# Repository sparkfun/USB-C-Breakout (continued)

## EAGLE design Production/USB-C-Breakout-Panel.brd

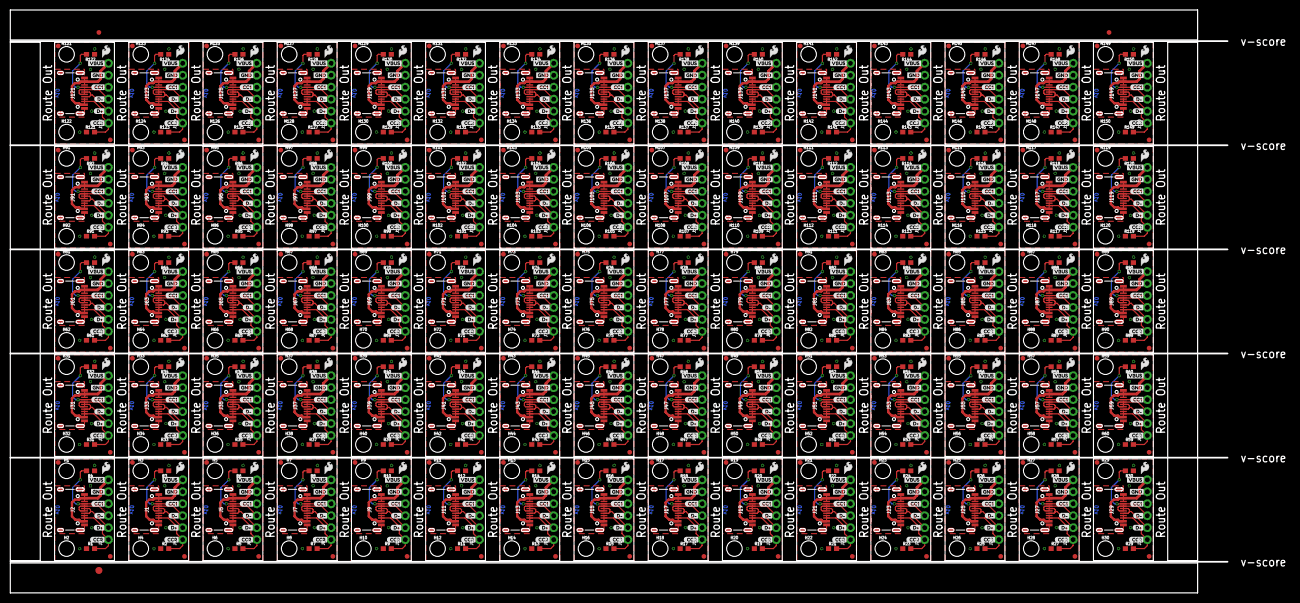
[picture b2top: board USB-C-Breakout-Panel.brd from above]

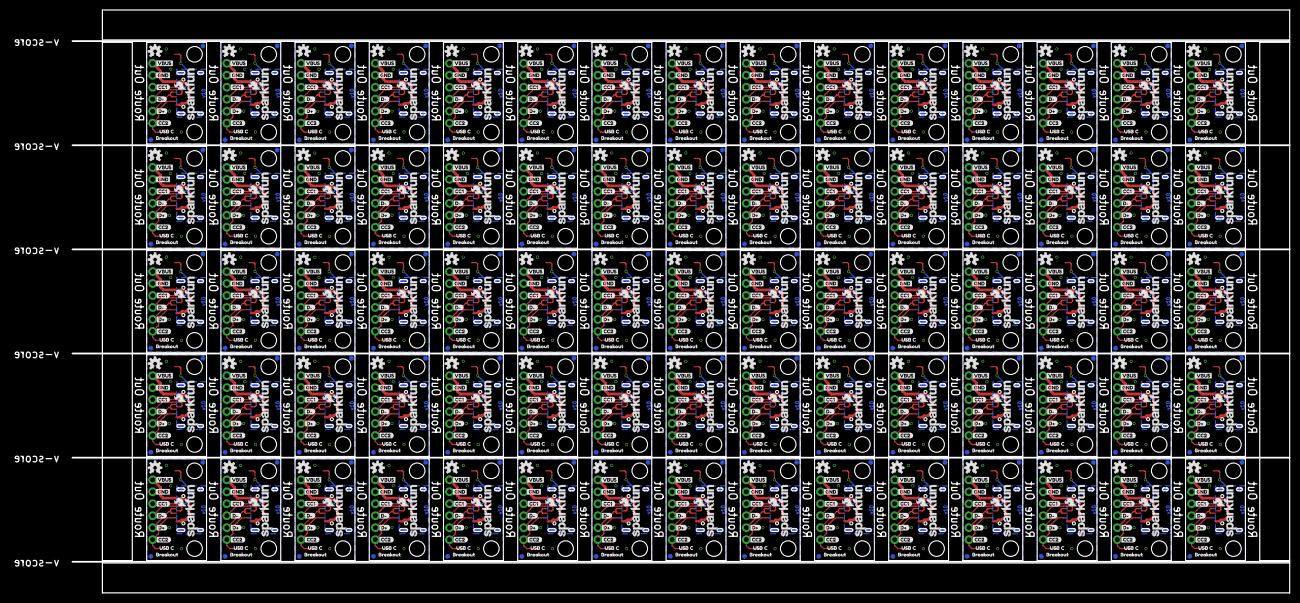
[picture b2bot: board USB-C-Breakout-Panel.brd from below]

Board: 2 copper layers, 258.3 x 123.7 mm, 2028 parts (900 on the bottom side), 525 nets.

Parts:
E$1, E$2: FIDUCIAL-1X2
E$3: FIDUCIAL-1.5X3
H1, H2, H3, H4, H5, H6, H7, H8, H9, H10, H11, H12, H13, H14, H15, H16, H17, H18, H19, H20, H21, H22, H23, H24, H25, H26, H27, H28, H29, H30, H31, H32, H33, H34, H35, H36, H37, H38, H39, H40, H41, H42, H43, H44, H45, H46, H47, H48, H49, H50, H51, H52, H53, H54, H55, H56, H57, H58, H59, H60, H61, H62, H63, H64, H65, H66, H67, H68, H69, H70, H71, H72, H73, H74, H75, H76, H77, H78, H79, H80, H81, H82, H83, H84, H85, H86, H87, H88, H89, H90, H91, H92, H93, H94, H95, H96, H97, H98, H99, H100, H101, H102, H103, H104, H105, H106, H107, H108, H109, H110, H111, H112, H113, H114, H115, H116, H117, H118, H119, H120, H121, H122, H123, H124, H125, H126, H127, H128, H129, H130, H131, H132, H133, H134, H135, H136, H137, H138, H139, H140, H141, H142, H143, H144, H145, H146, H147, H148, H149, H150: STAND-OFF
J1, J2, J5, J7, J9, J11, J13, J15, J17, J19, J21, J23, J25, J27, J29, J31, J33, J35, J37, J39, J41, J43, J45, J47, J49, J51, J53, J55, J57, J59, J61, J63, J65, J67, J69, J71, J73, J75, J77, J79, J81, J83, J85, J87, J89, J91, J93, J95, J97, J99, J101, J103, J105, J107, J109, J111, J113, J115, J117, J119, J121, J123, J125, J127, J129, J131, J133, J135, J137, J139, J141, J143, J145, J147, J149: USB-C-16P
J3, J4, J6, J8, J10, J12, J14, J16, J18, J20, J22, J24, J26, J28, J30, J32, J34, J36, J38, J40, J42, J44, J46, J48, J50, J52, J54, J56, J58, J60, J62, J64, J66, J68, J70, J72, J74, J76, J78, J80, J82, J84, J86, J88, J90, J92, J94, J96, J98, J100, J102, J104, J106, J108, J110, J112, J114, J116, J118, J120, J122, J124, J126, J128, J130, J132, J134, J136, J138, J140, J142, J144, J146, J148, J150: 1X06_NO_SILK
JP1, JP2, JP3, JP4, JP5, JP6, JP7, JP8, JP9, JP10, JP11, JP12, JP13, JP14, JP15, JP16, JP17, JP18, JP19, JP20, JP21, JP22, JP23, JP24, JP25, JP26, JP27, JP28, JP29, JP30, JP31, JP32, JP33, JP34, JP35, JP36, JP37, JP38, JP39, JP40, JP41, JP42, JP43, JP44, JP45, JP46, JP47, JP48, JP49, JP50, JP51, JP52, JP53, JP54, JP55, JP56, JP57, JP58, JP59, JP60, JP61, JP62, JP63, JP64, JP65, JP66, JP67, JP68, JP69, JP70, JP71, JP72, JP73, JP74, JP75, JP76, JP77, JP78, JP79, JP80, JP81, JP82, JP83, JP84, JP85, JP86, JP87, JP88, JP89, JP90, JP91, JP92, JP93, JP94, JP95, JP96, JP97, JP98, JP99, JP100, JP101, JP102, JP103, JP104, JP105, JP106, JP107, JP108, JP109, JP110, JP111, JP112, JP113, JP114, JP115, JP116, JP117, JP118, JP119, JP120, JP121, JP122, JP123, JP124, JP125, JP126, JP127, JP128, JP129, JP130, JP131, JP132, JP133, JP134, JP135, JP136, JP137, JP138, JP139, JP140, JP141, JP142, JP143, JP144, JP145, JP146, JP147, JP148, JP149, JP150, JP151, JP152, JP153, JP154, JP155, JP156, JP157, JP158, JP159, JP160, JP161, JP162, JP163, JP164, JP165, JP166, JP167, JP168, JP169, JP170, JP171, JP172, JP173, JP174, JP175, JP176, JP177, JP178, JP179, JP180, JP181, JP182, JP183, JP184, JP185, JP186, JP187, JP188, JP189, JP190, JP191, JP192, JP193, JP194, JP195, JP196, JP197, JP198, JP199, JP200, JP201, JP202, JP203, JP204, JP205, JP206, JP207, JP208, JP209, JP210, JP211, JP212, JP213, JP214, JP215, JP216, JP217, JP218, JP219, JP220, JP221, JP222, JP223, JP224, JP225, JP226, JP227, JP228, JP229, JP230, JP231, JP232, JP233, JP234, JP235, JP236, JP237, JP238, JP239, JP240, JP241, JP242, JP243, JP244, JP245, JP246, JP247, JP248, JP249, JP250, JP251, JP252, JP253, JP254, JP255, JP256, JP257, JP258, JP259, JP260, JP261, JP262, JP263, JP264, JP265, JP266, JP267, JP268, JP269, JP270, JP271, JP272, JP273, JP274, JP275, JP276, JP277, JP278, JP279, JP280, JP281, JP282, JP283, JP284, JP285, JP286, JP287, JP288, JP289, JP290, JP291, JP292, JP293, JP294, JP295, JP296, JP297, JP298, JP299, JP300: FIDUCIAL1X2; FIDUCIAL-1X2
LOGO1, LOGO3, LOGO7, LOGO10, LOGO13, LOGO16, LOGO19, LOGO22, LOGO25, LOGO28, LOGO31, LOGO34, LOGO37, LOGO40, LOGO43, LOGO46, LOGO49, LOGO52, LOGO55, LOGO58, LOGO61, LOGO64, LOGO67, LOGO70, LOGO73, LOGO76, LOGO79, LOGO82, LOGO85, LOGO88, LOGO91, LOGO94, LOGO97, LOGO100, LOGO103, LOGO106, LOGO109, LOGO112, LOGO115, LOGO118, LOGO121, LOGO124, LOGO127, LOGO130, LOGO133, LOGO136, LOGO139, LOGO142, LOGO145, LOGO148, LOGO151, LOGO154, LOGO157, LOGO160, LOGO163, LOGO166, LOGO169, LOGO172, LOGO175, LOGO178, LOGO181, LOGO184, LOGO187, LOGO190, LOGO193, LOGO196, LOGO199, LOGO202, LOGO205, LOGO208, LOGO211, LOGO214, LOGO217, LOGO220, LOGO223: OSHW-LOGOS; OSHW-LOGO-S
LOGO2, LOGO5, LOGO8, LOGO11, LOGO14, LOGO17, LOGO20, LOGO23, LOGO26, LOGO29, LOGO32, LOGO35, LOGO38, LOGO41, LOGO44, LOGO47, LOGO50, LOGO53, LOGO56, LOGO59, LOGO62, LOGO65, LOGO68, LOGO71, LOGO74, LOGO77, LOGO80, LOGO83, LOGO86, LOGO89, LOGO92, LOGO95, LOGO98, LOGO101, LOGO104, LOGO107, LOGO110, LOGO113, LOGO116, LOGO119, LOGO122, LOGO125, LOGO128, LOGO131, LOGO134, LOGO137, LOGO140, LOGO143, LOGO146, LOGO149, LOGO152, LOGO155, LOGO158, LOGO161, LOGO164, LOGO167, LOGO170, LOGO173, LOGO176, LOGO179, LOGO182, LOGO185, LOGO188, LOGO191, LOGO194, LOGO197, LOGO200, LOGO203, LOGO206, LOGO209, LOGO212, LOGO215, LOGO218, LOGO221, LOGO224: SFE_LOGO_FLAME.1_INCH; SFE_LOGO_FLAME_.1
LOGO4, LOGO6, LOGO9, LOGO12, LOGO15, LOGO18, LOGO21, LOGO24, LOGO27, LOGO30, LOGO33, LOGO36, LOGO39, LOGO42, LOGO45, LOGO48, LOGO51, LOGO54, LOGO57, LOGO60, LOGO63, LOGO66, LOGO69, LOGO72, LOGO75, LOGO78, LOGO81, LOGO84, LOGO87, LOGO90, LOGO93, LOGO96, LOGO99, LOGO102, LOGO105, LOGO108, LOGO111, LOGO114, LOGO117, LOGO120, LOGO123, LOGO126, LOGO129, LOGO132, LOGO135, LOGO138, LOGO141, LOGO144, LOGO147, LOGO150, LOGO153, LOGO156, LOGO159, LOGO162, LOGO165, LOGO168, LOGO171, LOGO174, LOGO177, LOGO180, LOGO183, LOGO186, LOGO189, LOGO192, LOGO195, LOGO198, LOGO201, LOGO204, LOGO207, LOGO210, LOGO213, LOGO216, LOGO219, LOGO222, LOGO225: SFE_LOGO_NAME_FLAME.1_INCH; SFE_LOGO_NAME_FLAME_.1
R1, R2, R3, R4, R5, R6, R7, R8, R9, R10, R11, R12, R13, R14, R15, R16, R17, R18, R19, R20, R21, R22, R23, R24, R25, R26, R27, R28, R29, R30, R31, R32, R33, R34, R35, R36, R37, R38, R39, R40, R41, R42, R43, R44, R45, R46, R47, R48, R49, R50, R51, R52, R53, R54, R55, R56, R57, R58, R59, R60, R61, R62, R63, R64, R65, R66, R67, R68, R69, R70, R71, R72, R73, R74, R75, R76, R77, R78, R79, R80, R81, R82, R83, R84, R85, R86, R87, R88, R89, R90, R91, R92, R93, R94, R95, R96, R97, R98, R99, R100, R101, R102, R103, R104, R105, R106, R107, R108, R109, R110, R111, R112, R113, R114, R115, R116, R117, R118, R119, R120, R121, R122, R123, R124, R125, R126, R127, R128, R129, R130, R131, R132, R133, R134, R135, R136, R137, R138, R139, R140, R141, R142, R143, R144, R145, R146, R147, R148, R149, R150: 5.1k; 0603
U$1, U$11, U$23, U$26, U$37, U$40, U$51, U$54, U$65, U$68, U$79, U$82, U$93, U$96, U$107, U$110, U$121, U$124, U$135, U$138, U$149, U$152, U$163, U$166, U$177, U$180, U$191, U$194, U$205, U$208, U$219, U$222, U$233, U$236, U$247, U$250, U$261, U$264, U$275, U$278, U$289, U$292, U$303, U$306, U$317, U$320, U$331, U$334, U$345, U$348, U$359, U$362, U$373, U$376, U$387, U$390, U$401, U$404, U$415, U$418, U$429, U$432, U$443, U$446, U$457, U$460, U$471, U$474, U$485, U$488, U$499, U$502, U$513, U$516, U$527, U$530, U$541, U$544, U$555, U$558, U$569, U$572, U$583, U$586, U$597, U$600, U$611, U$614, U$625, U$628, U$639, U$642, U$653, U$656, U$667, U$670, U$681, U$684, U$695, U$698, U$709, U$712, U$723, U$726, U$737, U$740, U$751, U$754, U$765, U$768, U$779, U$782, U$793, U$796, U$807, U$810, U$821, U$824, U$835, U$838, U$849, U$852, U$863, U$866, U$877, U$880, U$891, U$894, U$905, U$908, U$919, U$922, U$933, U$936, U$947, U$950, U$961, U$964, U$975, U$978, U$989, U$992, U$1003, U$1006, U$1017, U$1020, U$1031, U$1034, U$1045, U$1048: GND2
U$2, U$27, U$41, U$55, U$69, U$83, U$97, U$111, U$125, U$139, U$153, U$167, U$181, U$195, U$209, U$223, U$237, U$251, U$265, U$279, U$293, U$307, U$321, U$335, U$349, U$363, U$377, U$391, U$405, U$419, U$433, U$447, U$461, U$475, U$489, U$503, U$517, U$531, U$545, U$559, U$573, U$587, U$601, U$615, U$629, U$643, U$657, U$671, U$685, U$699, U$713, U$727, U$741, U$755, U$769, U$783, U$797, U$811, U$825, U$839, U$853, U$867, U$881, U$895, U$909, U$923, U$937, U$951, U$965, U$979, U$993, U$1007, U$1021, U$1035, U$1049: BREAKOUT1
U$3, U$15, U$29, U$43, U$57, U$71, U$85, U$99, U$113, U$127, U$141, U$155, U$169, U$183, U$197, U$211, U$225, U$239, U$253, U$267, U$281, U$295, U$309, U$323, U$337, U$351, U$365, U$379, U$393, U$407, U$421, U$435, U$449, U$463, U$477, U$491, U$505, U$519, U$533, U$547, U$561, U$575, U$589, U$603, U$617, U$631, U$645, U$659, U$673, U$687, U$701, U$715, U$729, U$743, U$757, U$771, U$785, U$799, U$813, U$827, U$841, U$855, U$869, U$883, U$897, U$911, U$925, U$939, U$953, U$967, U$981, U$995, U$1009, U$1023, U$1037: CC10
U$4, U$16, U$30, U$44, U$58, U$72, U$86, U$100, U$114, U$128, U$142, U$156, U$170, U$184, U$198, U$212, U$226, U$240, U$254, U$268, U$282, U$296, U$310, U$324, U$338, U$352, U$366, U$380, U$394, U$408, U$422, U$436, U$450, U$464, U$478, U$492, U$506, U$520, U$534, U$548, U$562, U$576, U$590, U$604, U$618, U$632, U$646, U$660, U$674, U$688, U$702, U$716, U$730, U$744, U$758, U$772, U$786, U$800, U$814, U$828, U$842, U$856, U$870, U$884, U$898, U$912, U$926, U$940, U$954, U$968, U$982, U$996, U$1010, U$1024, U$1038: CC14
U$5, U$17, U$31, U$45, U$59, U$73, U$87, U$101, U$115, U$129, U$143, U$157, U$171, U$185, U$199, U$213, U$227, U$241, U$255, U$269, U$283, U$297, U$311, U$325, U$339, U$353, U$367, U$381, U$395, U$409, U$423, U$437, U$451, U$465, U$479, U$493, U$507, U$521, U$535, U$549, U$563, U$577, U$591, U$605, U$619, U$633, U$647, U$661, U$675, U$689, U$703, U$717, U$731, U$745, U$759, U$773, U$787, U$801, U$815, U$829, U$843, U$857, U$871, U$885, U$899, U$913, U$927, U$941, U$955, U$969, U$983, U$997, U$1011, U$1025, U$1039: CC21
U$6, U$18, U$32, U$46, U$60, U$74, U$88, U$102, U$116, U$130, U$144, U$158, U$172, U$186, U$200, U$214, U$228, U$242, U$256, U$270, U$284, U$298, U$312, U$326, U$340, U$354, U$368, U$382, U$396, U$410, U$424, U$438, U$452, U$466, U$480, U$494, U$508, U$522, U$536, U$550, U$564, U$578, U$592, U$606, U$620, U$634, U$648, U$662, U$676, U$690, U$704, U$718, U$732, U$746, U$760, U$774, U$788, U$802, U$816, U$830, U$844, U$858, U$872, U$886, U$900, U$914, U$928, U$942, U$956, U$970, U$984, U$998, U$1012, U$1026, U$1040: CC25
U$7, U$19, U$33, U$47, U$61, U$75, U$89, U$103, U$117, U$131, U$145, U$159, U$173, U$187, U$201, U$215, U$229, U$243, U$257, U$271, U$285, U$299, U$313, U$327, U$341, U$355, U$369, U$383, U$397, U$411, U$425, U$439, U$453, U$467, U$481, U$495, U$509, U$523, U$537, U$551, U$565, U$579, U$593, U$607, U$621, U$635, U$649, U$663, U$677, U$691, U$705, U$719, U$733, U$747, U$761, U$775, U$789, U$803, U$817, U$831, U$845, U$859, U$873, U$887, U$901, U$915, U$929, U$943, U$957, U$971, U$985, U$999, U$1013, U$1027, U$1041: D#6
U$8, U$20, U$34, U$48, U$62, U$76, U$90, U$104, U$118, U$132, U$146, U$160, U$174, U$188, U$202, U$216, U$230, U$244, U$258, U$272, U$286, U$300, U$314, U$328, U$342, U$356, U$370, U$384, U$398, U$412, U$426, U$440, U$454, U$468, U$482, U$496, U$510, U$524, U$538, U$552, U$566, U$580, U$594, U$608, U$622, U$636, U$650, U$664, U$678, U$692, U$706, U$720, U$734, U$748, U$762, U$776, U$790, U$804, U$818, U$832, U$846, U$860, U$874, U$888, U$902, U$916, U$930, U$944, U$958, U$972, U$986, U$1000, U$1014, U$1028, U$1042: D#7
U$9, U$21, U$35, U$49, U$63, U$77, U$91, U$105, U$119, U$133, U$147, U$161, U$175, U$189, U$203, U$217, U$231, U$245, U$259, U$273, U$287, U$301, U$315, U$329, U$343, U$357, U$371, U$385, U$399, U$413, U$427, U$441, U$455, U$469, U$483, U$497, U$511, U$525, U$539, U$553, U$567, U$581, U$595, U$609, U$623, U$637, U$651, U$665, U$679, U$693, U$707, U$721, U$735, U$749, U$763, U$777, U$791, U$805, U$819, U$833, U$847, U$861, U$875, U$889, U$903, U$917, U$931, U$945, U$959, U$973, U$987, U$1001, U$1015, U$1029, U$1043: D#8
U$10, U$22, U$36, U$50, U$64, U$78, U$92, U$106, U$120, U$134, U$148, U$162, U$176, U$190, U$204, U$218, U$232, U$246, U$260, U$274, U$288, U$302, U$316, U$330, U$344, U$358, U$372, U$386, U$400, U$414, U$428, U$442, U$456, U$470, U$484, U$498, U$512, U$526, U$540, U$554, U$568, U$582, U$596, U$610, U$624, U$638, U$652, U$666, U$680, U$694, U$708, U$722, U$736, U$750, U$764, U$778, U$792, U$806, U$820, U$834, U$848, U$862, U$876, U$890, U$904, U$918, U$932, U$946, U$960, U$974, U$988, U$1002, U$1016, U$1030, U$1044: D#9
U$12, U$13, U$24, U$25, U$38, U$39, U$52, U$53, U$66, U$67, U$80, U$81, U$94, U$95, U$108, U$109, U$122, U$123, U$136, U$137, U$150, U$151, U$164, U$165, U$178, U$179, U$192, U$193, U$206, U$207, U$220, U$221, U$234, U$235, U$248, U$249, U$262, U$263, U$276, U$277, U$290, U$291, U$304, U$305, U$318, U$319, U$332, U$333, U$346, U$347, U$360, U$361, U$374, U$375, U$388, U$389, U$402, U$403, U$416, U$417, U$430, U$431, U$444, U$445, U$458, U$459, U$472, U$473, U$486, U$487, U$500, U$501, U$514, U$515, U$528, U$529, U$542, U$543, U$556, U$557, U$570, U$571, U$584, U$585, U$598, U$599, U$612, U$613, U$626, U$627, U$640, U$641, U$654, U$655, U$668, U$669, U$682, U$683, U$696, U$697, U$710, U$711, U$724, U$725, U$738, U$739, U$752, U$753, U$766, U$767, U$780, U$781, U$794, U$795, U$808, U$809, U$822, U$823, U$836, U$837, U$850, U$851, U$864, U$865, U$878, U$879, U$892, U$893, U$906, U$907, U$920, U$921, U$934, U$935, U$948, U$949, U$962, U$963, U$976, U$977, U$990, U$991, U$1004, U$1005, U$1018, U$1019, U$1032, U$1033, U$1046, U$1047: VBUS3
U$14, U$28, U$42, U$56, U$70, U$84, U$98, U$112, U$126, U$140, U$154, U$168, U$182, U$196, U$210, U$224, U$238, U$252, U$266, U$280, U$294, U$308, U$322, U$336, U$350, U$364, U$378, U$392, U$406, U$420, U$434, U$448, U$462, U$476, U$490, U$504, U$518, U$532, U$546, U$560, U$574, U$588, U$602, U$616, U$630, U$644, U$658, U$672, U$686, U$700, U$714, U$728, U$742, U$756, U$770, U$784, U$798, U$812, U$826, U$840, U$854, U$868, U$882, U$896, U$910, U$924, U$938, U$952, U$966, U$980, U$994, U$1008, U$1022, U$1036, U$1050: USB_C0

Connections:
CC1: J2.A5, J3.4, R4.2
CC2: J2.B5, J3.1, R1.2
CC3: J1.A5, J4.4, R3.2
CC4: J1.B5, J4.1, R2.2
CC5: J5.A5, J6.4, R6.2
CC6: J5.B5, J6.1, R5.2
CC7: J7.A5, J8.4, R8.2
CC8: J7.B5, J8.1, R7.2
CC9: J9.A5, J10.4, R10.2
CC10: J9.B5, J10.1, R9.2
CC11: J11.A5, J12.4, R12.2
CC12: J11.B5, J12.1, R11.2
CC13: J13.A5, J14.4, R14.2
CC14: J13.B5, J14.1, R13.2
CC15: J15.A5, J16.4, R16.2
CC16: J15.B5, J16.1, R15.2
CC17: J17.A5, J18.4, R18.2
CC18: J17.B5, J18.1, R17.2
CC19: J19.A5, J20.4, R20.2
CC20: J19.B5, J20.1, R19.2
CC21: J21.A5, J22.4, R22.2
CC22: J21.B5, J22.1, R21.2
CC23: J23.A5, J24.4, R24.2
CC24: J23.B5, J24.1, R23.2
CC25: J25.A5, J26.4, R26.2
CC26: J25.B5, J26.1, R25.2
CC27: J27.A5, J28.4, R28.2
CC28: J27.B5, J28.1, R27.2
CC29: J29.A5, J30.4, R30.2
CC30: J29.B5, J30.1, R29.2
CC31: J31.A5, J32.4, R32.2
CC32: J31.B5, J32.1, R31.2
CC33: J33.A5, J34.4, R34.2
CC34: J33.B5, J34.1, R33.2
CC35: J35.A5, J36.4, R36.2
CC36: J35.B5, J36.1, R35.2
CC37: J37.A5, J38.4, R38.2
CC38: J37.B5, J38.1, R37.2
CC39: J39.A5, J40.4, R40.2
CC40: J39.B5, J40.1, R39.2
CC41: J41.A5, J42.4, R42.2
CC42: J41.B5, J42.1, R41.2
CC43: J43.A5, J44.4, R44.2
CC44: J43.B5, J44.1, R43.2
CC45: J45.A5, J46.4, R46.2
CC46: J45.B5, J46.1, R45.2
CC47: J47.A5, J48.4, R48.2
CC48: J47.B5, J48.1, R47.2
CC49: J49.A5, J50.4, R50.2
CC50: J49.B5, J50.1, R49.2
CC51: J51.A5, J52.4, R52.2
CC52: J51.B5, J52.1, R51.2
CC53: J53.A5, J54.4, R54.2
CC54: J53.B5, J54.1, R53.2
CC55: J55.A5, J56.4, R56.2
CC56: J55.B5, J56.1, R55.2
CC57: J57.A5, J58.4, R58.2
CC58: J57.B5, J58.1, R57.2
CC59: J59.A5, J60.4, R60.2
CC60: J59.B5, J60.1, R59.2
CC61: J61.A5, J62.4, R62.2
CC62: J61.B5, J62.1, R61.2
CC63: J63.A5, J64.4, R64.2
CC64: J63.B5, J64.1, R63.2
CC65: J65.A5, J66.4, R66.2
CC66: J65.B5, J66.1, R65.2
CC67: J67.A5, J68.4, R68.2
CC68: J67.B5, J68.1, R67.2
CC69: J69.A5, J70.4, R70.2
CC70: J69.B5, J70.1, R69.2
CC71: J71.A5, J72.4, R72.2
CC72: J71.B5, J72.1, R71.2
CC73: J73.A5, J74.4, R74.2
CC74: J73.B5, J74.1, R73.2
CC75: J75.A5, J76.4, R76.2
CC76: J75.B5, J76.1, R75.2
CC77: J77.A5, J78.4, R78.2
CC78: J77.B5, J78.1, R77.2
CC79: J79.A5, J80.4, R80.2
CC80: J79.B5, J80.1, R79.2
CC81: J81.A5, J82.4, R82.2
CC82: J81.B5, J82.1, R81.2
CC83: J83.A5, J84.4, R84.2
CC84: J83.B5, J84.1, R83.2
CC85: J85.A5, J86.4, R86.2
CC86: J85.B5, J86.1, R85.2
CC87: J87.A5, J88.4, R88.2
CC88: J87.B5, J88.1, R87.2
CC89: J89.A5, J90.4, R90.2
CC90: J89.B5, J90.1, R89.2
CC91: J91.A5, J92.4, R92.2
CC92: J91.B5, J92.1, R91.2
CC93: J93.A5, J94.4, R94.2
CC94: J93.B5, J94.1, R93.2
CC95: J95.A5, J96.4, R96.2
CC96: J95.B5, J96.1, R95.2
CC97: J97.A5, J98.4, R98.2
CC98: J97.B5, J98.1, R97.2
CC99: J99.A5, J100.4, R100.2
CC100: J99.B5, J100.1, R99.2
CC101: J101.A5, J102.4, R102.2
CC102: J101.B5, J102.1, R101.2
CC103: J103.A5, J104.4, R104.2
CC104: J103.B5, J104.1, R103.2
CC105: J105.A5, J106.4, R106.2
CC106: J105.B5, J106.1, R105.2
CC107: J107.A5, J108.4, R108.2
CC108: J107.B5, J108.1, R107.2
CC109: J109.A5, J110.4, R110.2
CC110: J109.B5, J110.1, R109.2
CC111: J111.A5, J112.4, R112.2
CC112: J111.B5, J112.1, R111.2
CC113: J113.A5, J114.4, R114.2
CC114: J113.B5, J114.1, R113.2
CC115: J115.A5, J116.4, R116.2
CC116: J115.B5, J116.1, R115.2
CC117: J117.A5, J118.4, R118.2
CC118: J117.B5, J118.1, R117.2
CC119: J119.A5, J120.4, R120.2
CC120: J119.B5, J120.1, R119.2
CC121: J121.A5, J122.4, R122.2
CC122: J121.B5, J122.1, R121.2
CC123: J123.A5, J124.4, R124.2
CC124: J123.B5, J124.1, R123.2
CC125: J125.A5, J126.4, R126.2
CC126: J125.B5, J126.1, R125.2
CC127: J127.A5, J128.4, R128.2
CC128: J127.B5, J128.1, R127.2
CC129: J129.A5, J130.4, R130.2
CC130: J129.B5, J130.1, R129.2
CC131: J131.A5, J132.4, R132.2
CC132: J131.B5, J132.1, R131.2
CC133: J133.A5, J134.4, R134.2
CC134: J133.B5, J134.1, R133.2
CC135: J135.A5, J136.4, R136.2
CC136: J135.B5, J136.1, R135.2
CC137: J137.A5, J138.4, R138.2
CC138: J137.B5, J138.1, R137.2
CC139: J139.A5, J140.4, R140.2
CC140: J139.B5, J140.1, R139.2
CC141: J141.A5, J142.4, R142.2
CC142: J141.B5, J142.1, R141.2
CC143: J143.A5, J144.4, R144.2
CC144: J143.B5, J144.1, R143.2
CC145: J145.A5, J146.4, R146.2
CC146: J145.B5, J146.1, R145.2
CC147: J147.A5, J148.4, R148.2
CC148: J147.B5, J148.1, R147.2
CC149: J149.A5, J150.4, R150.2
CC150: J149.B5, J150.1, R149.2
D+: J2.A6, J2.B6, J3.2
D+1: J1.A6, J1.B6, J4.2
D+2: J5.A6, J5.B6, J6.2
D+3: J7.A6, J7.B6, J8.2
D+4: J9.A6, J9.B6, J10.2
D+5: J11.A6, J11.B6, J12.2
D+6: J13.A6, J13.B6, J14.2
D+7: J15.A6, J15.B6, J16.2
D+8: J17.A6, J17.B6, J18.2
D+9: J19.A6, J19.B6, J20.2
D+10: J21.A6, J21.B6, J22.2
D+11: J23.A6, J23.B6, J24.2
D+12: J25.A6, J25.B6, J26.2
D+13: J27.A6, J27.B6, J28.2
D+14: J29.A6, J29.B6, J30.2
D+15: J31.A6, J31.B6, J32.2
D+16: J33.A6, J33.B6, J34.2
D+17: J35.A6, J35.B6, J36.2
D+18: J37.A6, J37.B6, J38.2
D+19: J39.A6, J39.B6, J40.2
D+20: J41.A6, J41.B6, J42.2
D+21: J43.A6, J43.B6, J44.2
D+22: J45.A6, J45.B6, J46.2
D+23: J47.A6, J47.B6, J48.2
D+24: J49.A6, J49.B6, J50.2
D+25: J51.A6, J51.B6, J52.2
D+26: J53.A6, J53.B6, J54.2
D+27: J55.A6, J55.B6, J56.2
D+28: J57.A6, J57.B6, J58.2
D+29: J59.A6, J59.B6, J60.2
D+30: J61.A6, J61.B6, J62.2
D+31: J63.A6, J63.B6, J64.2
D+32: J65.A6, J65.B6, J66.2
D+33: J67.A6, J67.B6, J68.2
D+34: J69.A6, J69.B6, J70.2
D+35: J71.A6, J71.B6, J72.2
D+36: J73.A6, J73.B6, J74.2
D+37: J75.A6, J75.B6, J76.2
D+38: J77.A6, J77.B6, J78.2
D+39: J79.A6, J79.B6, J80.2
D+40: J81.A6, J81.B6, J82.2
D+41: J83.A6, J83.B6, J84.2
D+42: J85.A6, J85.B6, J86.2
D+43: J87.A6, J87.B6, J88.2
D+44: J89.A6, J89.B6, J90.2
D+45: J91.A6, J91.B6, J92.2
D+46: J93.A6, J93.B6, J94.2
D+47: J95.A6, J95.B6, J96.2
D+48: J97.A6, J97.B6, J98.2
D+49: J99.A6, J99.B6, J100.2
D+50: J101.A6, J101.B6, J102.2
D+51: J103.A6, J103.B6, J104.2
D+52: J105.A6, J105.B6, J106.2
D+53: J107.A6, J107.B6, J108.2
D+54: J109.A6, J109.B6, J110.2
D+55: J111.A6, J111.B6, J112.2
D+56: J113.A6, J113.B6, J114.2
D+57: J115.A6, J115.B6, J116.2
D+58: J117.A6, J117.B6, J118.2
D+59: J119.A6, J119.B6, J120.2
D+60: J121.A6, J121.B6, J122.2
D+61: J123.A6, J123.B6, J124.2
D+62: J125.A6, J125.B6, J126.2
D+63: J127.A6, J127.B6, J128.2
D+64: J129.A6, J129.B6, J130.2
D+65: J131.A6, J131.B6, J132.2
D+66: J133.A6, J133.B6, J134.2
D+67: J135.A6, J135.B6, J136.2
D+68: J137.A6, J137.B6, J138.2
D+69: J139.A6, J139.B6, J140.2
D+70: J141.A6, J141.B6, J142.2
D+71: J143.A6, J143.B6, J144.2
D+72: J145.A6, J145.B6, J146.2
D+73: J147.A6, J147.B6, J148.2
D+74: J149.A6, J149.B6, J150.2
D-: J2.A7, J2.B7, J3.3
D-1: J1.A7, J1.B7, J4.3
D-2: J5.A7, J5.B7, J6.3
D-3: J7.A7, J7.B7, J8.3
D-4: J9.A7, J9.B7, J10.3
D-5: J11.A7, J11.B7, J12.3
D-6: J13.A7, J13.B7, J14.3
D-7: J15.A7, J15.B7, J16.3
D-8: J17.A7, J17.B7, J18.3
D-9: J19.A7, J19.B7, J20.3
D-10: J21.A7, J21.B7, J22.3
D-11: J23.A7, J23.B7, J24.3
D-12: J25.A7, J25.B7, J26.3
D-13: J27.A7, J27.B7, J28.3
D-14: J29.A7, J29.B7, J30.3
D-15: J31.A7, J31.B7, J32.3
D-16: J33.A7, J33.B7, J34.3
D-17: J35.A7, J35.B7, J36.3
D-18: J37.A7, J37.B7, J38.3
D-19: J39.A7, J39.B7, J40.3
D-20: J41.A7, J41.B7, J42.3
D-21: J43.A7, J43.B7, J44.3
D-22: J45.A7, J45.B7, J46.3
D-23: J47.A7, J47.B7, J48.3
D-24: J49.A7, J49.B7, J50.3
D-25: J51.A7, J51.B7, J52.3
D-26: J53.A7, J53.B7, J54.3
D-27: J55.A7, J55.B7, J56.3
D-28: J57.A7, J57.B7, J58.3
D-29: J59.A7, J59.B7, J60.3
D-30: J61.A7, J61.B7, J62.3
D-31: J63.A7, J63.B7, J64.3
D-32: J65.A7, J65.B7, J66.3
D-33: J67.A7, J67.B7, J68.3
D-34: J69.A7, J69.B7, J70.3
D-35: J71.A7, J71.B7, J72.3
D-36: J73.A7, J73.B7, J74.3
D-37: J75.A7, J75.B7, J76.3
D-38: J77.A7, J77.B7, J78.3
D-39: J79.A7, J79.B7, J80.3
D-40: J81.A7, J81.B7, J82.3
D-41: J83.A7, J83.B7, J84.3
D-42: J85.A7, J85.B7, J86.3
D-43: J87.A7, J87.B7, J88.3
D-44: J89.A7, J89.B7, J90.3
D-45: J91.A7, J91.B7, J92.3
D-46: J93.A7, J93.B7, J94.3
D-47: J95.A7, J95.B7, J96.3
D-48: J97.A7, J97.B7, J98.3
D-49: J99.A7, J99.B7, J100.3
D-50: J101.A7, J101.B7, J102.3
D-51: J103.A7, J103.B7, J104.3
D-52: J105.A7, J105.B7, J106.3
D-53: J107.A7, J107.B7, J108.3
D-54: J109.A7, J109.B7, J110.3
D-55: J111.A7, J111.B7, J112.3
D-56: J113.A7, J113.B7, J114.3
D-57: J115.A7, J115.B7, J116.3
D-58: J117.A7, J117.B7, J118.3
D-59: J119.A7, J119.B7, J120.3
D-60: J121.A7, J121.B7, J122.3
D-61: J123.A7, J123.B7, J124.3
D-62: J125.A7, J125.B7, J126.3
D-63: J127.A7, J127.B7, J128.3
D-64: J129.A7, J129.B7, J130.3
D-65: J131.A7, J131.B7, J132.3
D-66: J133.A7, J133.B7, J134.3
D-67: J135.A7, J135.B7, J136.3
D-68: J137.A7, J137.B7, J138.3
D-69: J139.A7, J139.B7, J140.3
D-70: J141.A7, J141.B7, J142.3
D-71: J143.A7, J143.B7, J144.3
D-72: J145.A7, J145.B7, J146.3
D-73: J147.A7, J147.B7, J148.3
D-74: J149.A7, J149.B7, J150.3
GND: J2.GND, J2.GND2, J3.5, R1.1, R4.1
GND1: J1.GND, J1.GND2, J4.5, R2.1, R3.1
GND2: J5.GND, J5.GND2, J6.5, R5.1, R6.1
GND3: J7.GND, J7.GND2, J8.5, R7.1, R8.1
GND4: J9.GND, J9.GND2, J10.5, R9.1, R10.1
GND5: J11.GND, J11.GND2, J12.5, R11.1, R12.1
GND6: J13.GND, J13.GND2, J14.5, R13.1, R14.1
GND7: J15.GND, J15.GND2, J16.5, R15.1, R16.1
GND8: J17.GND, J17.GND2, J18.5, R17.1, R18.1
GND9: J19.GND, J19.GND2, J20.5, R19.1, R20.1
GND10: J21.GND, J21.GND2, J22.5, R21.1, R22.1
GND11: J23.GND, J23.GND2, J24.5, R23.1, R24.1
GND12: J25.GND, J25.GND2, J26.5, R25.1, R26.1
GND13: J27.GND, J27.GND2, J28.5, R27.1, R28.1
GND14: J29.GND, J29.GND2, J30.5, R29.1, R30.1
GND15: J31.GND, J31.GND2, J32.5, R31.1, R32.1
GND16: J33.GND, J33.GND2, J34.5, R33.1, R34.1
GND17: J35.GND, J35.GND2, J36.5, R35.1, R36.1
GND18: J37.GND, J37.GND2, J38.5, R37.1, R38.1
GND19: J39.GND, J39.GND2, J40.5, R39.1, R40.1
GND20: J41.GND, J41.GND2, J42.5, R41.1, R42.1
GND21: J43.GND, J43.GND2, J44.5, R43.1, R44.1
GND22: J45.GND, J45.GND2, J46.5, R45.1, R46.1
GND23: J47.GND, J47.GND2, J48.5, R47.1, R48.1
GND24: J49.GND, J49.GND2, J50.5, R49.1, R50.1
GND25: J51.GND, J51.GND2, J52.5, R51.1, R52.1
GND26: J53.GND, J53.GND2, J54.5, R53.1, R54.1
GND27: J55.GND, J55.GND2, J56.5, R55.1, R56.1
GND28: J57.GND, J57.GND2, J58.5, R57.1, R58.1
GND29: J59.GND, J59.GND2, J60.5, R59.1, R60.1
GND30: J61.GND, J61.GND2, J62.5, R61.1, R62.1
GND31: J63.GND, J63.GND2, J64.5, R63.1, R64.1
GND32: J65.GND, J65.GND2, J66.5, R65.1, R66.1
GND33: J67.GND, J67.GND2, J68.5, R67.1, R68.1
GND34: J69.GND, J69.GND2, J70.5, R69.1, R70.1
GND35: J71.GND, J71.GND2, J72.5, R71.1, R72.1
GND36: J73.GND, J73.GND2, J74.5, R73.1, R74.1
GND37: J75.GND, J75.GND2, J76.5, R75.1, R76.1
GND38: J77.GND, J77.GND2, J78.5, R77.1, R78.1
GND39: J79.GND, J79.GND2, J80.5, R79.1, R80.1
GND40: J81.GND, J81.GND2, J82.5, R81.1, R82.1
GND41: J83.GND, J83.GND2, J84.5, R83.1, R84.1
GND42: J85.GND, J85.GND2, J86.5, R85.1, R86.1
GND43: J87.GND, J87.GND2, J88.5, R87.1, R88.1
GND44: J89.GND, J89.GND2, J90.5, R89.1, R90.1
GND45: J91.GND, J91.GND2, J92.5, R91.1, R92.1
GND46: J93.GND, J93.GND2, J94.5, R93.1, R94.1
GND47: J95.GND, J95.GND2, J96.5, R95.1, R96.1
GND48: J97.GND, J97.GND2, J98.5, R97.1, R98.1
GND49: J99.GND, J99.GND2, J100.5, R99.1, R100.1
GND50: J101.GND, J101.GND2, J102.5, R101.1, R102.1
GND51: J103.GND, J103.GND2, J104.5, R103.1, R104.1
GND52: J105.GND, J105.GND2, J106.5, R105.1, R106.1
GND53: J107.GND, J107.GND2, J108.5, R107.1, R108.1
GND54: J109.GND, J109.GND2, J110.5, R109.1, R110.1
GND55: J111.GND, J111.GND2, J112.5, R111.1, R112.1
GND56: J113.GND, J113.GND2, J114.5, R113.1, R114.1
GND57: J115.GND, J115.GND2, J116.5, R115.1, R116.1
GND58: J117.GND, J117.GND2, J118.5, R117.1, R118.1
GND59: J119.GND, J119.GND2, J120.5, R119.1, R120.1
GND60: J121.GND, J121.GND2, J122.5, R121.1, R122.1
GND61: J123.GND, J123.GND2, J124.5, R123.1, R124.1
GND62: J125.GND, J125.GND2, J126.5, R125.1, R126.1
GND63: J127.GND, J127.GND2, J128.5, R127.1, R128.1
GND64: J129.GND, J129.GND2, J130.5, R129.1, R130.1
GND65: J131.GND, J131.GND2, J132.5, R131.1, R132.1
GND66: J133.GND, J133.GND2, J134.5, R133.1, R134.1
GND67: J135.GND, J135.GND2, J136.5, R135.1, R136.1
GND68: J137.GND, J137.GND2, J138.5, R137.1, R138.1
GND69: J139.GND, J139.GND2, J140.5, R139.1, R140.1
GND70: J141.GND, J141.GND2, J142.5, R141.1, R142.1
GND71: J143.GND, J143.GND2, J144.5, R143.1, R144.1
GND72: J145.GND, J145.GND2, J146.5, R145.1, R146.1
GND73: J147.GND, J147.GND2, J148.5, R147.1, R148.1
GND74: J149.GND, J149.GND2, J150.5, R149.1, R150.1
SHLD: J2.SHLD1, J2.SHLD2, J2.SHLD3, J2.SHLD4, J2.SHLD5, J2.SHLD6, J2.SHLD7, J2.SHLD8
SHLD1: J1.SHLD1, J1.SHLD2, J1.SHLD3, J1.SHLD4, J1.SHLD5, J1.SHLD6, J1.SHLD7, J1.SHLD8
SHLD2: J5.SHLD1, J5.SHLD2, J5.SHLD3, J5.SHLD4, J5.SHLD5, J5.SHLD6, J5.SHLD7, J5.SHLD8
SHLD3: J7.SHLD1, J7.SHLD2, J7.SHLD3, J7.SHLD4, J7.SHLD5, J7.SHLD6, J7.SHLD7, J7.SHLD8
SHLD4: J9.SHLD1, J9.SHLD2, J9.SHLD3, J9.SHLD4, J9.SHLD5, J9.SHLD6, J9.SHLD7, J9.SHLD8
SHLD5: J11.SHLD1, J11.SHLD2, J11.SHLD3, J11.SHLD4, J11.SHLD5, J11.SHLD6, J11.SHLD7, J11.SHLD8
SHLD6: J13.SHLD1, J13.SHLD2, J13.SHLD3, J13.SHLD4, J13.SHLD5, J13.SHLD6, J13.SHLD7, J13.SHLD8
SHLD7: J15.SHLD1, J15.SHLD2, J15.SHLD3, J15.SHLD4, J15.SHLD5, J15.SHLD6, J15.SHLD7, J15.SHLD8
SHLD8: J17.SHLD1, J17.SHLD2, J17.SHLD3, J17.SHLD4, J17.SHLD5, J17.SHLD6, J17.SHLD7, J17.SHLD8
SHLD9: J19.SHLD1, J19.SHLD2, J19.SHLD3, J19.SHLD4, J19.SHLD5, J19.SHLD6, J19.SHLD7, J19.SHLD8
SHLD10: J21.SHLD1, J21.SHLD2, J21.SHLD3, J21.SHLD4, J21.SHLD5, J21.SHLD6, J21.SHLD7, J21.SHLD8
SHLD11: J23.SHLD1, J23.SHLD2, J23.SHLD3, J23.SHLD4, J23.SHLD5, J23.SHLD6, J23.SHLD7, J23.SHLD8
SHLD12: J25.SHLD1, J25.SHLD2, J25.SHLD3, J25.SHLD4, J25.SHLD5, J25.SHLD6, J25.SHLD7, J25.SHLD8
SHLD13: J27.SHLD1, J27.SHLD2, J27.SHLD3, J27.SHLD4, J27.SHLD5, J27.SHLD6, J27.SHLD7, J27.SHLD8
SHLD14: J29.SHLD1, J29.SHLD2, J29.SHLD3, J29.SHLD4, J29.SHLD5, J29.SHLD6, J29.SHLD7, J29.SHLD8
SHLD15: J31.SHLD1, J31.SHLD2, J31.SHLD3, J31.SHLD4, J31.SHLD5, J31.SHLD6, J31.SHLD7, J31.SHLD8
SHLD16: J33.SHLD1, J33.SHLD2, J33.SHLD3, J33.SHLD4, J33.SHLD5, J33.SHLD6, J33.SHLD7, J33.SHLD8
SHLD17: J35.SHLD1, J35.SHLD2, J35.SHLD3, J35.SHLD4, J35.SHLD5, J35.SHLD6, J35.SHLD7, J35.SHLD8
SHLD18: J37.SHLD1, J37.SHLD2, J37.SHLD3, J37.SHLD4, J37.SHLD5, J37.SHLD6, J37.SHLD7, J37.SHLD8
SHLD19: J39.SHLD1, J39.SHLD2, J39.SHLD3, J39.SHLD4, J39.SHLD5, J39.SHLD6, J39.SHLD7, J39.SHLD8
SHLD20: J41.SHLD1, J41.SHLD2, J41.SHLD3, J41.SHLD4, J41.SHLD5, J41.SHLD6, J41.SHLD7, J41.SHLD8
SHLD21: J43.SHLD1, J43.SHLD2, J43.SHLD3, J43.SHLD4, J43.SHLD5, J43.SHLD6, J43.SHLD7, J43.SHLD8
SHLD22: J45.SHLD1, J45.SHLD2, J45.SHLD3, J45.SHLD4, J45.SHLD5, J45.SHLD6, J45.SHLD7, J45.SHLD8
SHLD23: J47.SHLD1, J47.SHLD2, J47.SHLD3, J47.SHLD4, J47.SHLD5, J47.SHLD6, J47.SHLD7, J47.SHLD8
SHLD24: J49.SHLD1, J49.SHLD2, J49.SHLD3, J49.SHLD4, J49.SHLD5, J49.SHLD6, J49.SHLD7, J49.SHLD8
SHLD25: J51.SHLD1, J51.SHLD2, J51.SHLD3, J51.SHLD4, J51.SHLD5, J51.SHLD6, J51.SHLD7, J51.SHLD8
SHLD26: J53.SHLD1, J53.SHLD2, J53.SHLD3, J53.SHLD4, J53.SHLD5, J53.SHLD6, J53.SHLD7, J53.SHLD8
SHLD27: J55.SHLD1, J55.SHLD2, J55.SHLD3, J55.SHLD4, J55.SHLD5, J55.SHLD6, J55.SHLD7, J55.SHLD8
SHLD28: J57.SHLD1, J57.SHLD2, J57.SHLD3, J57.SHLD4, J57.SHLD5, J57.SHLD6, J57.SHLD7, J57.SHLD8
SHLD29: J59.SHLD1, J59.SHLD2, J59.SHLD3, J59.SHLD4, J59.SHLD5, J59.SHLD6, J59.SHLD7, J59.SHLD8
SHLD30: J61.SHLD1, J61.SHLD2, J61.SHLD3, J61.SHLD4, J61.SHLD5, J61.SHLD6, J61.SHLD7, J61.SHLD8
SHLD31: J63.SHLD1, J63.SHLD2, J63.SHLD3, J63.SHLD4, J63.SHLD5, J63.SHLD6, J63.SHLD7, J63.SHLD8
SHLD32: J65.SHLD1, J65.SHLD2, J65.SHLD3, J65.SHLD4, J65.SHLD5, J65.SHLD6, J65.SHLD7, J65.SHLD8
SHLD33: J67.SHLD1, J67.SHLD2, J67.SHLD3, J67.SHLD4, J67.SHLD5, J67.SHLD6, J67.SHLD7, J67.SHLD8
SHLD34: J69.SHLD1, J69.SHLD2, J69.SHLD3, J69.SHLD4, J69.SHLD5, J69.SHLD6, J69.SHLD7, J69.SHLD8
SHLD35: J71.SHLD1, J71.SHLD2, J71.SHLD3, J71.SHLD4, J71.SHLD5, J71.SHLD6, J71.SHLD7, J71.SHLD8
SHLD36: J73.SHLD1, J73.SHLD2, J73.SHLD3, J73.SHLD4, J73.SHLD5, J73.SHLD6, J73.SHLD7, J73.SHLD8
SHLD37: J75.SHLD1, J75.SHLD2, J75.SHLD3, J75.SHLD4, J75.SHLD5, J75.SHLD6, J75.SHLD7, J75.SHLD8
SHLD38: J77.SHLD1, J77.SHLD2, J77.SHLD3, J77.SHLD4, J77.SHLD5, J77.SHLD6, J77.SHLD7, J77.SHLD8
SHLD39: J79.SHLD1, J79.SHLD2, J79.SHLD3, J79.SHLD4, J79.SHLD5, J79.SHLD6, J79.SHLD7, J79.SHLD8
SHLD40: J81.SHLD1, J81.SHLD2, J81.SHLD3, J81.SHLD4, J81.SHLD5, J81.SHLD6, J81.SHLD7, J81.SHLD8
SHLD41: J83.SHLD1, J83.SHLD2, J83.SHLD3, J83.SHLD4, J83.SHLD5, J83.SHLD6, J83.SHLD7, J83.SHLD8
SHLD42: J85.SHLD1, J85.SHLD2, J85.SHLD3, J85.SHLD4, J85.SHLD5, J85.SHLD6, J85.SHLD7, J85.SHLD8
SHLD43: J87.SHLD1, J87.SHLD2, J87.SHLD3, J87.SHLD4, J87.SHLD5, J87.SHLD6, J87.SHLD7, J87.SHLD8
SHLD44: J89.SHLD1, J89.SHLD2, J89.SHLD3, J89.SHLD4, J89.SHLD5, J89.SHLD6, J89.SHLD7, J89.SHLD8
SHLD45: J91.SHLD1, J91.SHLD2, J91.SHLD3, J91.SHLD4, J91.SHLD5, J91.SHLD6, J91.SHLD7, J91.SHLD8
SHLD46: J93.SHLD1, J93.SHLD2, J93.SHLD3, J93.SHLD4, J93.SHLD5, J93.SHLD6, J93.SHLD7, J93.SHLD8
SHLD47: J95.SHLD1, J95.SHLD2, J95.SHLD3, J95.SHLD4, J95.SHLD5, J95.SHLD6, J95.SHLD7, J95.SHLD8
SHLD48: J97.SHLD1, J97.SHLD2, J97.SHLD3, J97.SHLD4, J97.SHLD5, J97.SHLD6, J97.SHLD7, J97.SHLD8
SHLD49: J99.SHLD1, J99.SHLD2, J99.SHLD3, J99.SHLD4, J99.SHLD5, J99.SHLD6, J99.SHLD7, J99.SHLD8
SHLD50: J101.SHLD1, J101.SHLD2, J101.SHLD3, J101.SHLD4, J101.SHLD5, J101.SHLD6, J101.SHLD7, J101.SHLD8
SHLD51: J103.SHLD1, J103.SHLD2, J103.SHLD3, J103.SHLD4, J103.SHLD5, J103.SHLD6, J103.SHLD7, J103.SHLD8
SHLD52: J105.SHLD1, J105.SHLD2, J105.SHLD3, J105.SHLD4, J105.SHLD5, J105.SHLD6, J105.SHLD7, J105.SHLD8
SHLD53: J107.SHLD1, J107.SHLD2, J107.SHLD3, J107.SHLD4, J107.SHLD5, J107.SHLD6, J107.SHLD7, J107.SHLD8
SHLD54: J109.SHLD1, J109.SHLD2, J109.SHLD3, J109.SHLD4, J109.SHLD5, J109.SHLD6, J109.SHLD7, J109.SHLD8
SHLD55: J111.SHLD1, J111.SHLD2, J111.SHLD3, J111.SHLD4, J111.SHLD5, J111.SHLD6, J111.SHLD7, J111.SHLD8
SHLD56: J113.SHLD1, J113.SHLD2, J113.SHLD3, J113.SHLD4, J113.SHLD5, J113.SHLD6, J113.SHLD7, J113.SHLD8
SHLD57: J115.SHLD1, J115.SHLD2, J115.SHLD3, J115.SHLD4, J115.SHLD5, J115.SHLD6, J115.SHLD7, J115.SHLD8
SHLD58: J117.SHLD1, J117.SHLD2, J117.SHLD3, J117.SHLD4, J117.SHLD5, J117.SHLD6, J117.SHLD7, J117.SHLD8
SHLD59: J119.SHLD1, J119.SHLD2, J119.SHLD3, J119.SHLD4, J119.SHLD5, J119.SHLD6, J119.SHLD7, J119.SHLD8
SHLD60: J121.SHLD1, J121.SHLD2, J121.SHLD3, J121.SHLD4, J121.SHLD5, J121.SHLD6, J121.SHLD7, J121.SHLD8
SHLD61: J123.SHLD1, J123.SHLD2, J123.SHLD3, J123.SHLD4, J123.SHLD5, J123.SHLD6, J123.SHLD7, J123.SHLD8
SHLD62: J125.SHLD1, J125.SHLD2, J125.SHLD3, J125.SHLD4, J125.SHLD5, J125.SHLD6, J125.SHLD7, J125.SHLD8
SHLD63: J127.SHLD1, J127.SHLD2, J127.SHLD3, J127.SHLD4, J127.SHLD5, J127.SHLD6, J127.SHLD7, J127.SHLD8
SHLD64: J129.SHLD1, J129.SHLD2, J129.SHLD3, J129.SHLD4, J129.SHLD5, J129.SHLD6, J129.SHLD7, J129.SHLD8
SHLD65: J131.SHLD1, J131.SHLD2, J131.SHLD3, J131.SHLD4, J131.SHLD5, J131.SHLD6, J131.SHLD7, J131.SHLD8
SHLD66: J133.SHLD1, J133.SHLD2, J133.SHLD3, J133.SHLD4, J133.SHLD5, J133.SHLD6, J133.SHLD7, J133.SHLD8
SHLD67: J135.SHLD1, J135.SHLD2, J135.SHLD3, J135.SHLD4, J135.SHLD5, J135.SHLD6, J135.SHLD7, J135.SHLD8
SHLD68: J137.SHLD1, J137.SHLD2, J137.SHLD3, J137.SHLD4, J137.SHLD5, J137.SHLD6, J137.SHLD7, J137.SHLD8
SHLD69: J139.SHLD1, J139.SHLD2, J139.SHLD3, J139.SHLD4, J139.SHLD5, J139.SHLD6, J139.SHLD7, J139.SHLD8
SHLD70: J141.SHLD1, J141.SHLD2, J141.SHLD3, J141.SHLD4, J141.SHLD5, J141.SHLD6, J141.SHLD7, J141.SHLD8
SHLD71: J143.SHLD1, J143.SHLD2, J143.SHLD3, J143.SHLD4, J143.SHLD5, J143.SHLD6, J143.SHLD7, J143.SHLD8
SHLD72: J145.SHLD1, J145.SHLD2, J145.SHLD3, J145.SHLD4, J145.SHLD5, J145.SHLD6, J145.SHLD7, J145.SHLD8
SHLD73: J147.SHLD1, J147.SHLD2, J147.SHLD3, J147.SHLD4, J147.SHLD5, J147.SHLD6, J147.SHLD7, J147.SHLD8
SHLD74: J149.SHLD1, J149.SHLD2, J149.SHLD3, J149.SHLD4, J149.SHLD5, J149.SHLD6, J149.SHLD7, J149.SHLD8
VBUS: J2.VBUS1, J2.VBUS2, J3.6
VBUS1: J1.VBUS1, J1.VBUS2, J4.6
VBUS2: J5.VBUS1, J5.VBUS2, J6.6
VBUS3: J7.VBUS1, J7.VBUS2, J8.6
VBUS4: J9.VBUS1, J9.VBUS2, J10.6
VBUS5: J11.VBUS1, J11.VBUS2, J12.6
VBUS6: J13.VBUS1, J13.VBUS2, J14.6
VBUS7: J15.VBUS1, J15.VBUS2, J16.6
VBUS8: J17.VBUS1, J17.VBUS2, J18.6
VBUS9: J19.VBUS1, J19.VBUS2, J20.6
VBUS10: J21.VBUS1, J21.VBUS2, J22.6
VBUS11: J23.VBUS1, J23.VBUS2, J24.6
VBUS12: J25.VBUS1, J25.VBUS2, J26.6
VBUS13: J27.VBUS1, J27.VBUS2, J28.6
VBUS14: J29.VBUS1, J29.VBUS2, J30.6
VBUS15: J31.VBUS1, J31.VBUS2, J32.6
VBUS16: J33.VBUS1, J33.VBUS2, J34.6
VBUS17: J35.VBUS1, J35.VBUS2, J36.6
VBUS18: J37.VBUS1, J37.VBUS2, J38.6
VBUS19: J39.VBUS1, J39.VBUS2, J40.6
VBUS20: J41.VBUS1, J41.VBUS2, J42.6
VBUS21: J43.VBUS1, J43.VBUS2, J44.6
VBUS22: J45.VBUS1, J45.VBUS2, J46.6
VBUS23: J47.VBUS1, J47.VBUS2, J48.6
VBUS24: J49.VBUS1, J49.VBUS2, J50.6
VBUS25: J51.VBUS1, J51.VBUS2, J52.6
VBUS26: J53.VBUS1, J53.VBUS2, J54.6
VBUS27: J55.VBUS1, J55.VBUS2, J56.6
VBUS28: J57.VBUS1, J57.VBUS2, J58.6
VBUS29: J59.VBUS1, J59.VBUS2, J60.6
VBUS30: J61.VBUS1, J61.VBUS2, J62.6
VBUS31: J63.VBUS1, J63.VBUS2, J64.6
VBUS32: J65.VBUS1, J65.VBUS2, J66.6
VBUS33: J67.VBUS1, J67.VBUS2, J68.6
VBUS34: J69.VBUS1, J69.VBUS2, J70.6
VBUS35: J71.VBUS1, J71.VBUS2, J72.6
VBUS36: J73.VBUS1, J73.VBUS2, J74.6
VBUS37: J75.VBUS1, J75.VBUS2, J76.6
VBUS38: J77.VBUS1, J77.VBUS2, J78.6
VBUS39: J79.VBUS1, J79.VBUS2, J80.6
VBUS40: J81.VBUS1, J81.VBUS2, J82.6
VBUS41: J83.VBUS1, J83.VBUS2, J84.6
VBUS42: J85.VBUS1, J85.VBUS2, J86.6
VBUS43: J87.VBUS1, J87.VBUS2, J88.6
VBUS44: J89.VBUS1, J89.VBUS2, J90.6
VBUS45: J91.VBUS1, J91.VBUS2, J92.6
VBUS46: J93.VBUS1, J93.VBUS2, J94.6
VBUS47: J95.VBUS1, J95.VBUS2, J96.6
VBUS48: J97.VBUS1, J97.VBUS2, J98.6
VBUS49: J99.VBUS1, J99.VBUS2, J100.6
VBUS50: J101.VBUS1, J101.VBUS2, J102.6
VBUS51: J103.VBUS1, J103.VBUS2, J104.6
VBUS52: J105.VBUS1, J105.VBUS2, J106.6
VBUS53: J107.VBUS1, J107.VBUS2, J108.6
VBUS54: J109.VBUS1, J109.VBUS2, J110.6
VBUS55: J111.VBUS1, J111.VBUS2, J112.6
VBUS56: J113.VBUS1, J113.VBUS2, J114.6
VBUS57: J115.VBUS1, J115.VBUS2, J116.6
VBUS58: J117.VBUS1, J117.VBUS2, J118.6
VBUS59: J119.VBUS1, J119.VBUS2, J120.6
VBUS60: J121.VBUS1, J121.VBUS2, J122.6
VBUS61: J123.VBUS1, J123.VBUS2, J124.6
VBUS62: J125.VBUS1, J125.VBUS2, J126.6
VBUS63: J127.VBUS1, J127.VBUS2, J128.6
VBUS64: J129.VBUS1, J129.VBUS2, J130.6
VBUS65: J131.VBUS1, J131.VBUS2, J132.6
VBUS66: J133.VBUS1, J133.VBUS2, J134.6
VBUS67: J135.VBUS1, J135.VBUS2, J136.6
VBUS68: J137.VBUS1, J137.VBUS2, J138.6
VBUS69: J139.VBUS1, J139.VBUS2, J140.6
VBUS70: J141.VBUS1, J141.VBUS2, J142.6
VBUS71: J143.VBUS1, J143.VBUS2, J144.6
VBUS72: J145.VBUS1, J145.VBUS2, J146.6
VBUS73: J147.VBUS1, J147.VBUS2, J148.6
VBUS74: J149.VBUS1, J149.VBUS2, J150.6

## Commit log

2018-11-12 Updated library, tidied up schematic, deleted unneccesary files, and added readme
2018-11-14 Add board dimensions to measures layer
2018-12-06 Add Hardware Folder Path
